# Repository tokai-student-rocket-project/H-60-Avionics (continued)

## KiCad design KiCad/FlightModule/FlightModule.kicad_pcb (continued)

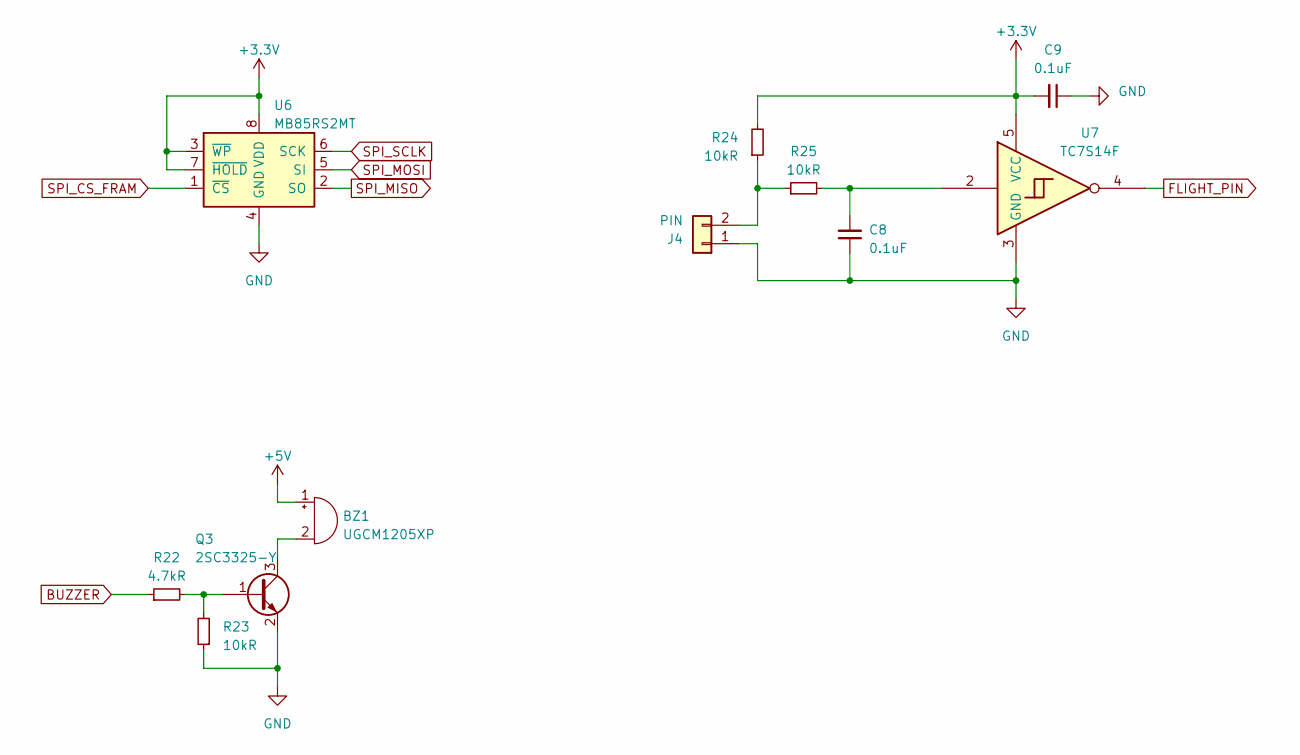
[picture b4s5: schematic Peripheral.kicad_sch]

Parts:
BZ1: UGCM1205XP; Buzzer_12x9.5RM7.6
C8, C9: 0.1uF; C_0603_1608Metric_Pad1.08x0.95mm_HandSolder
J4: PIN; Hirose_DF1B
Q3: 2SC3325-Y; SC-59_Handsoldering
R22: 4.7kR; R_0603_1608Metric_Pad0.98x0.95mm_HandSolder
R23, R24, R25: 10kR; R_0603_1608Metric_Pad0.98x0.95mm_HandSolder
U6: MB85RS2MT; DIP-8_W7.62mm
U7: TC7S14F; TSOT-23-5_HandSoldering

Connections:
+3.3V: C9.2, R24.2, U6.3 (~WP), U6.7 (~HOLD), U6.8 (VDD), U7.5 (VCC); also elsewhere on the board
+5V: BZ1.1 (-); also elsewhere on the board
BUZZER: R22.1; also elsewhere on the board
FLIGHT_PIN: U7.4; also elsewhere on the board
GND: C8.1, C9.1, J4.1, Q3.2 (E), R23.1, U6.4 (GND), U7.3 (GND); also elsewhere on the board
unnamed: BZ1.2 (+), Q3.3 (C)
unnamed: C8.2, R25.2, U7.2
unnamed: J4.2, R24.1, R25.1
unnamed: Q3.1 (B), R22.2, R23.2
SPI_CS_FRAM: U6.1 (~CS); also elsewhere on the board
SPI_MISO: U6.2 (SO); also elsewhere on the board
SPI_MOSI: U6.5 (SI); also elsewhere on the board
SPI_SCLK: U6.6 (SCK); also elsewhere on the board

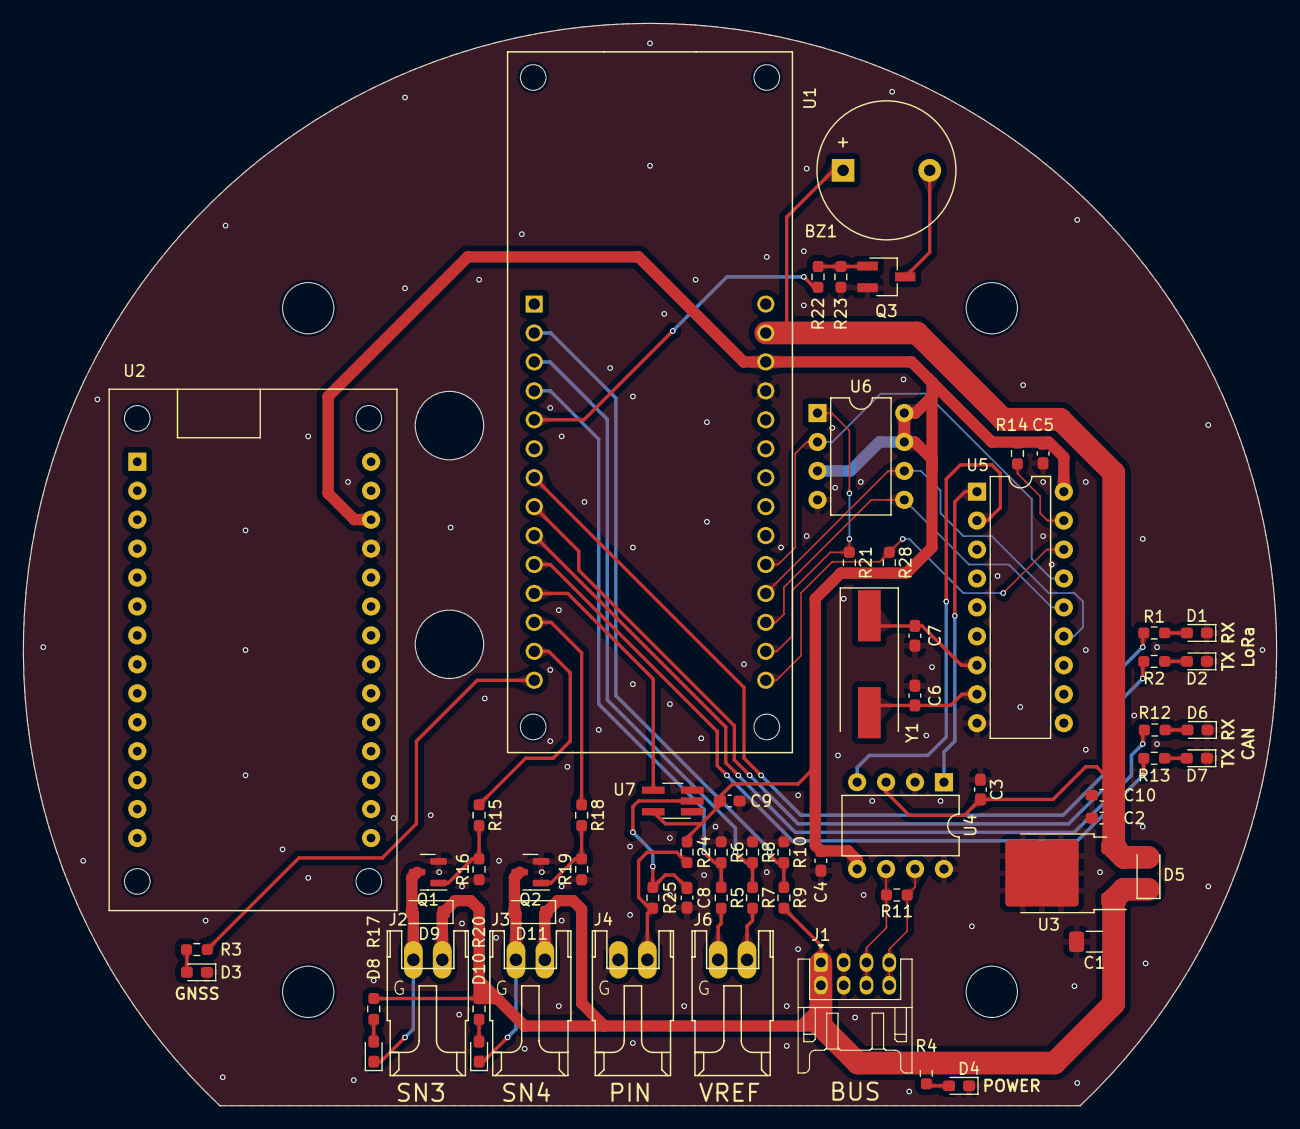
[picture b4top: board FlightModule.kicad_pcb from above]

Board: 2 copper layers, 110.0 x 95.0 mm, 64 parts (0 on the bottom side), 46 nets.

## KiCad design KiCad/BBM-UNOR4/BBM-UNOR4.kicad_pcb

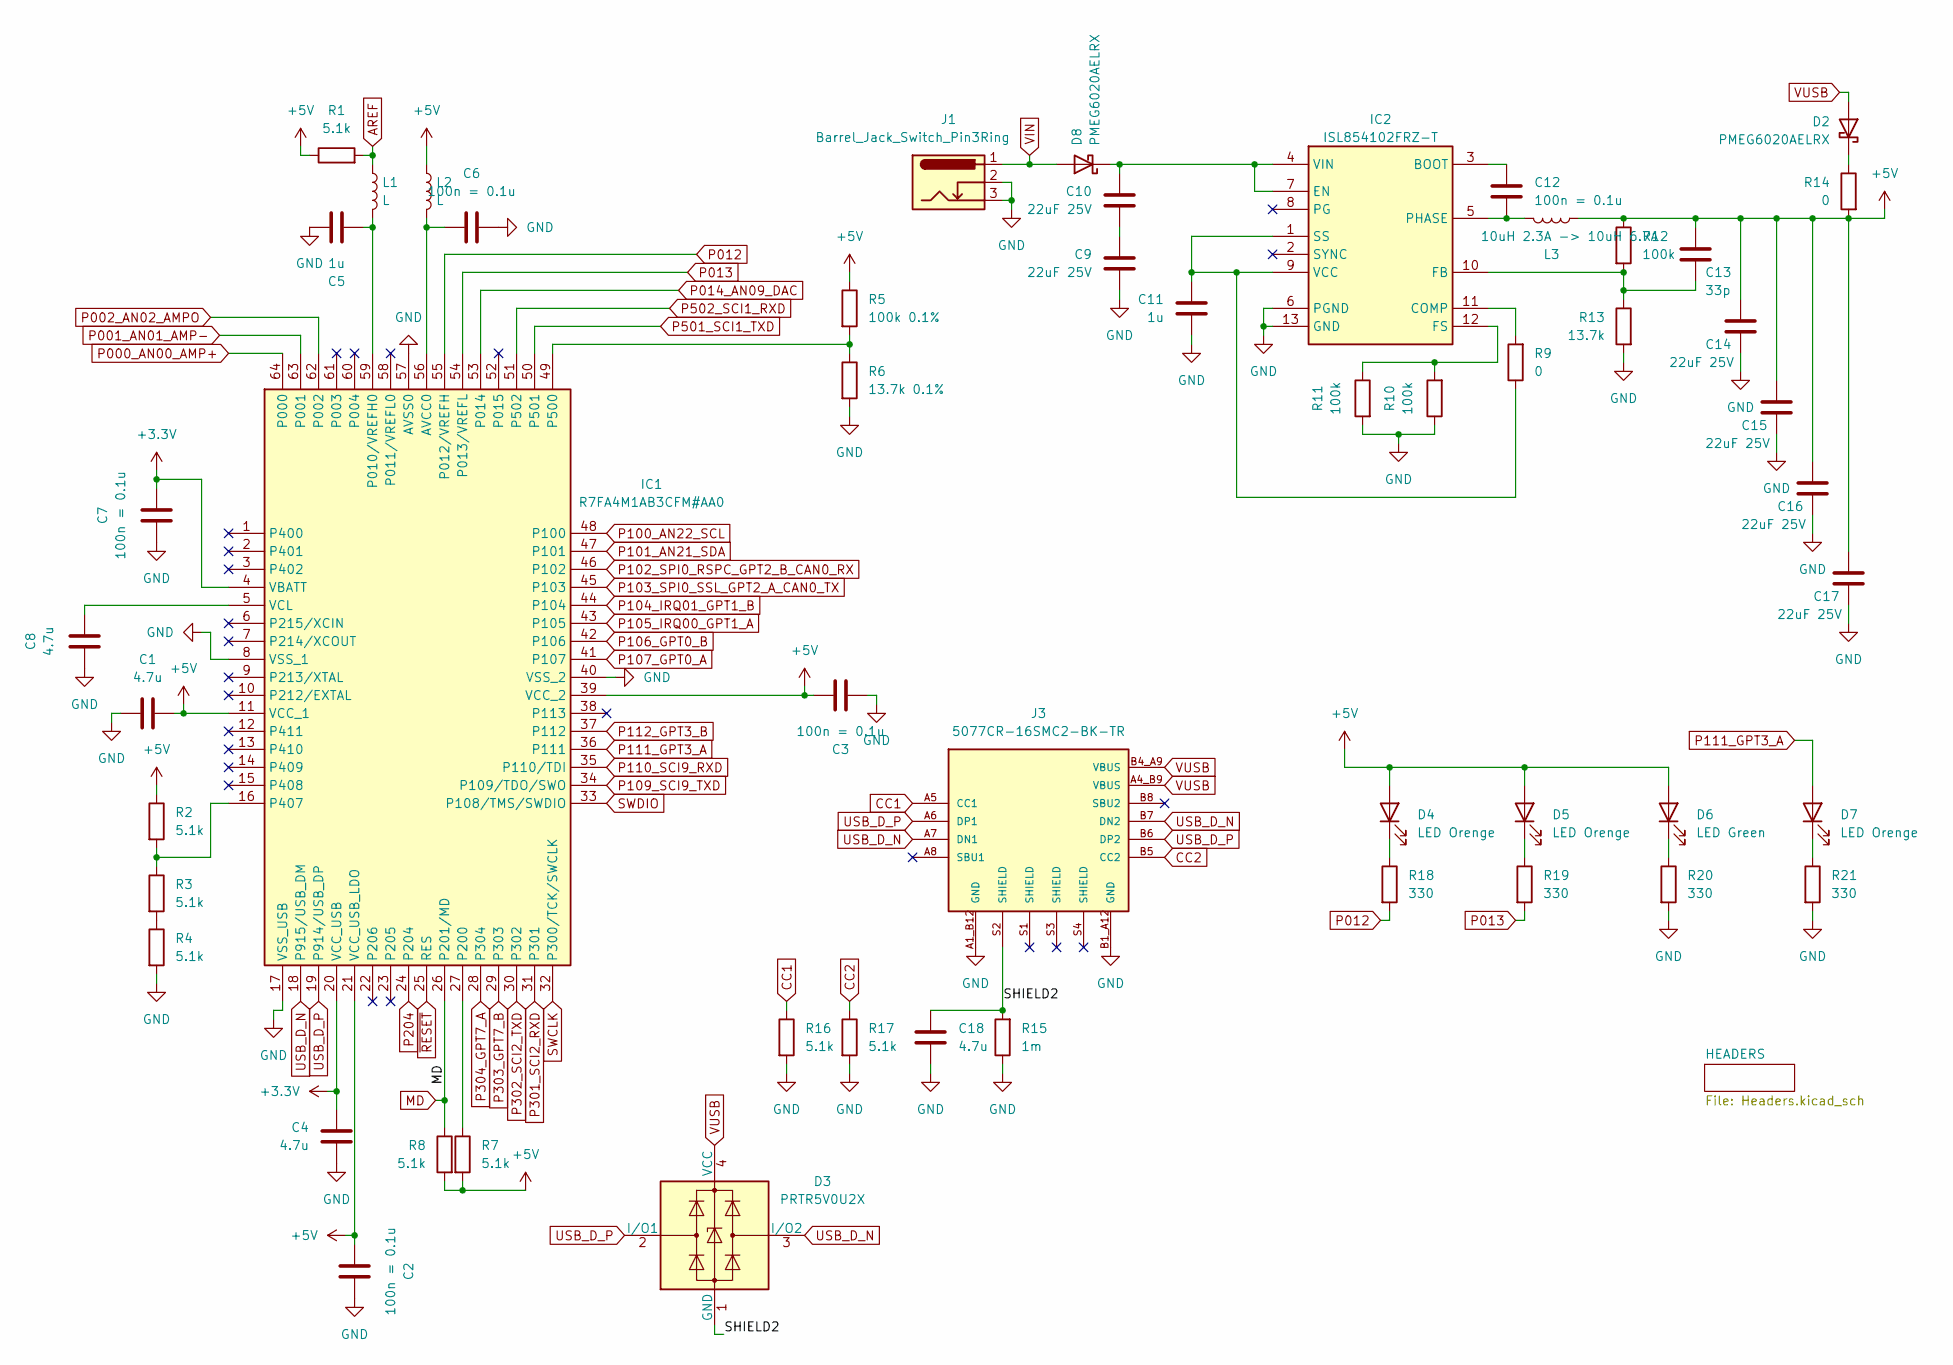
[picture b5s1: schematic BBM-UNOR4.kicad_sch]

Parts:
C1, C4, C8, C18: 4.7u; C_0805_2012Metric
C2, C3, C6, C7, C12: 100n = 0.1u; C_0603_1608Metric
C5, C11: 1u; C_0603_1608Metric
C9, C10, C14, C15, C16, C17: 22uF 25V; C_0805_2012Metric
C13: 33p; C_0603_1608Metric
D2, D8: PMEG6020AELRX; Nexperia_CFP3_SOD-123W
D3: PRTR5V0U2X; SOT-143
D4, D5, D7: LED Orenge; LED_0603_1608Metric
D6: LED Green; LED_0603_1608Metric
IC1: R7FA4M1AB3CFM#AA0; QFP50P1200X1200X170-64N; Manufacturer_Part_Number R7FA4M1AB3CFM#AA0; Mouser Part Number 968-7FA4M1AB3CFM#AA0
IC2: ISL854102FRZ-T; SON50P300X400X100-13N-D; Manufacturer_Part_Number ISL854102FRZ-T; Mouser Part Number 968-ISL854102FRZ-T
J1: Barrel_Jack_Switch_Pin3Ring; BarrelJack_Horizontal
J3: 5077CR-16SMC2-BK-TR; NELTRON_5077CR-16SMC2-BK-TR
L1, L2: L; C_0603_1608Metric
L3: 10uH 2.3A -> 10uH 6.7A; L_12x12mm_H8mm
R1, R2, R3, R4, R7, R8, R16, R17: 5.1k; R_0603_1608Metric
R5: 100k 0.1%; R_0603_1608Metric
R6: 13.7k 0.1%; R_0603_1608Metric
R9, R14: 0; R_0603_1608Metric
R10, R11, R12: 100k; R_0603_1608Metric
R13: 13.7k; R_0603_1608Metric
R15: 1m; R_0805_2012Metric
R18, R19, R20, R21: 330; R_0603_1608Metric

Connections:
+3.3V: C4.2, C7.2, IC1.4 (VBATT), IC1.20 (VCC_USB); also elsewhere on the board
+5V: C1.2, C2.2, C3.1, C13.1, C14.1, C15.2, C16.2, C17.2, D4.2 (A), D5.2 (A), D6.2 (A), IC1.11 (VCC_1), IC1.21 (VCC_USB_LDO), IC1.39 (VCC_2), L2.1, L3.2, R1.1, R2.1, R5.1, R7.2, R8.2, R12.1, R14.2; also elsewhere on the board
/SHIELD2: C18.1, D3.1 (GND), J3.S2 (SHIELD), R15.2
AREF: L1.1, R1.2; also elsewhere on the board
CC1: J3.A5 (CC1), R16.1
CC2: J3.B5 (CC2), R17.1
GND: C1.1, C2.1, C3.2, C4.1, C5.2, C6.1, C7.1, C8.1, C9.2, C11.2, C14.2, C15.1, C16.1, C17.1, C18.2, IC1.8 (VSS_1), IC1.17 (VSS_USB), IC1.40 (VSS_2), IC1.57 (AVSS0), IC2.6 (PGND), IC2.13 (GND), J1.2, J1.3, J3.A1_B12 (GND), J3.B1_A12 (GND), R4.2, R6.2, R10.1, R11.2, R13.2, R15.1, R16.2, R17.2, R20.2, R21.2; also elsewhere on the board
MD: IC1.26 (P201/MD), R8.1; also elsewhere on the board
unnamed: C9.1, C10.2
unnamed: D2.1 (K), R14.1
unnamed: D4.1 (K), R18.1
unnamed: D5.1 (K), R19.1
unnamed: D6.1 (K), R20.1
unnamed: D7.1 (K), R21.1
unnamed: C10.1, D8.1 (K), IC2.4 (VIN), IC2.7 (EN)
unnamed: C6.2, IC1.56 (AVCC0), L2.2
unnamed: C5.1, IC1.59 (P010/VREFH0), L1.2
unnamed: IC1.27 (P200), R7.1
unnamed: IC1.16 (P407), R2.2, R3.1
unnamed: IC1.49 (P500), R5.2, R6.1
unnamed: C8.2, IC1.5 (VCL)
unnamed: C12.1, IC2.3 (BOOT)
unnamed: IC2.11 (COMP), R9.2
unnamed: C13.2, IC2.10 (FB), R12.2, R13.1
unnamed: IC2.12 (FS), R10.2, R11.1
unnamed: C12.2, IC2.5 (PHASE), L3.1
unnamed: C11.1, IC2.1 (SS), IC2.9 (VCC), R9.1
unnamed: R3.2, R4.1
P000_AN00_AMP+: IC1.64 (P000); also elsewhere on the board
P001_AN01_AMP-: IC1.63 (P001); also elsewhere on the board
P002_AN02_AMPO: IC1.62 (P002); also elsewhere on the board
P012: IC1.55 (P012/VREFH), R18.2
P013: IC1.54 (P013/VREFL), R19.2
P014_AN09_DAC: IC1.53 (P014); also elsewhere on the board
P100_AN22_SCL: IC1.48 (P100); also elsewhere on the board
P101_AN21_SDA: IC1.47 (P101); also elsewhere on the board
P102_SPI0_RSPC_GPT2_B_CAN0_RX: IC1.46 (P102); also elsewhere on the board
P103_SPI0_SSL_GPT2_A_CAN0_TX: IC1.45 (P103); also elsewhere on the board
P104_IRQ01_GPT1_B: IC1.44 (P104); also elsewhere on the board
P105_IRQ00_GPT1_A: IC1.43 (P105); also elsewhere on the board
P106_GPT0_B: IC1.42 (P106); also elsewhere on the board
P107_GPT0_A: IC1.41 (P107); also elsewhere on the board
P109_SCI9_TXD: IC1.34 (P109/TDO/SWO); also elsewhere on the board
P110_SCI9_RXD: IC1.35 (P110/TDI); also elsewhere on the board
P111_GPT3_A: D7.2 (A), IC1.36 (P111); also elsewhere on the board
P112_GPT3_B: IC1.37 (P112); also elsewhere on the board
P204: IC1.24 (P204)
P301_SCI2_RXD: IC1.31 (P301); also elsewhere on the board
P302_SCI2_TXD: IC1.30 (P302); also elsewhere on the board
P303_GPT7_B: IC1.29 (P303); also elsewhere on the board
P304_GPT7_A: IC1.28 (P304); also elsewhere on the board
P501_SCI1_TXD: IC1.50 (P501)
P502_SCI1_RXD: IC1.51 (P502)
SWCLK: IC1.32 (P300/TCK/SWCLK)
SWDIO: IC1.33 (P108/TMS/SWDIO)
USB_D_N: D3.3 (I/O2), IC1.18 (P915/USB_DM), J3.A7 (DN1), J3.B7 (DN2)
USB_D_P: D3.2 (I/O1), IC1.19 (P914/USB_DP), J3.A6 (DP1), J3.B6 (DP2)
VIN: D8.2 (A), J1.1; also elsewhere on the board
VUSB: D2.2 (A), D3.4 (VCC), J3.A4_B9 (VBUS), J3.B4_A9 (VBUS)
~RESET: IC1.25 (RES); also elsewhere on the board

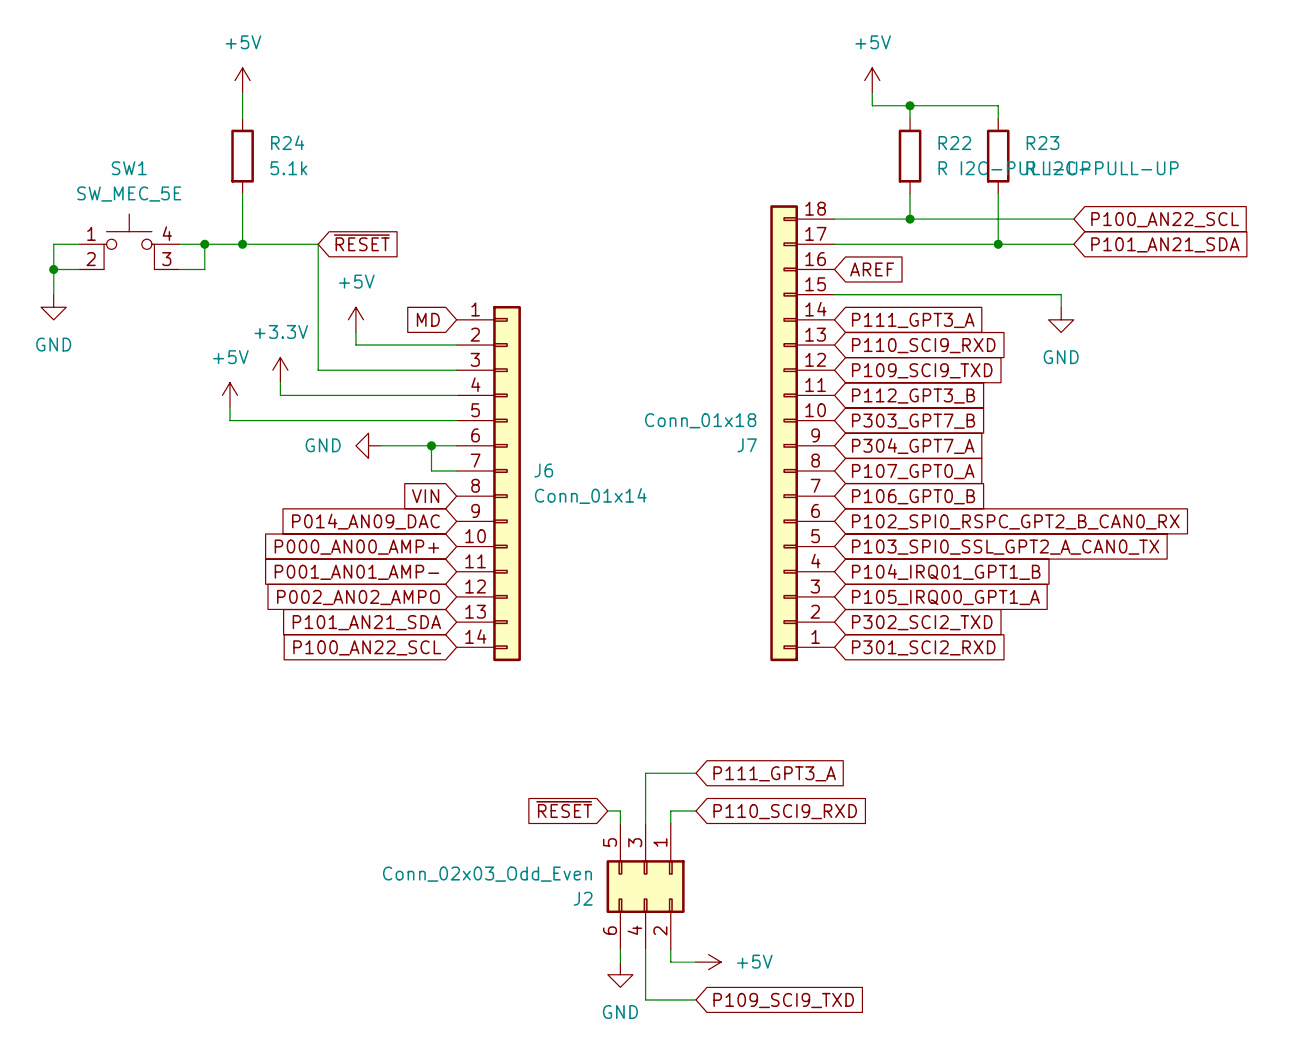
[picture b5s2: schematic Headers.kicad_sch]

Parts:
J2: Conn_02x03_Odd_Even; IDC-Header_2x03_P2.54mm_Vertical
J6: Conn_01x14; PinSocket_1x14_P2.54mm_Vertical
J7: Conn_01x18; PinSocket_1x18_P2.54mm_Vertical
R22, R23: R I2C-PULL-UP; R_0603_1608Metric
R24: 5.1k; R_0603_1608Metric
SW1: SW_MEC_5E; SMT_4.2X3.2_

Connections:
+3.3V: J6.4; also elsewhere on the board
+5V: J2.2, J6.2, J6.5, R22.1, R23.1, R24.1; also elsewhere on the board
AREF: J7.16; also elsewhere on the board
GND: J2.6, J6.6, J6.7, J7.15, SW1.1, SW1.2; also elsewhere on the board
MD: J6.1; also elsewhere on the board
P000_AN00_AMP+: J6.10; also elsewhere on the board
P001_AN01_AMP-: J6.11; also elsewhere on the board
P002_AN02_AMPO: J6.12; also elsewhere on the board
P014_AN09_DAC: J6.9; also elsewhere on the board
P100_AN22_SCL: J6.14, J7.18, R22.2; also elsewhere on the board
P101_AN21_SDA: J6.13, J7.17, R23.2; also elsewhere on the board
P102_SPI0_RSPC_GPT2_B_CAN0_RX: J7.6; also elsewhere on the board
P103_SPI0_SSL_GPT2_A_CAN0_TX: J7.5; also elsewhere on the board
P104_IRQ01_GPT1_B: J7.4; also elsewhere on the board
P105_IRQ00_GPT1_A: J7.3; also elsewhere on the board
P106_GPT0_B: J7.7; also elsewhere on the board
P107_GPT0_A: J7.8; also elsewhere on the board
P109_SCI9_TXD: J2.4, J7.12; also elsewhere on the board
P110_SCI9_RXD: J2.1, J7.13; also elsewhere on the board
P111_GPT3_A: J2.3, J7.14; also elsewhere on the board
P112_GPT3_B: J7.11; also elsewhere on the board
P301_SCI2_RXD: J7.1; also elsewhere on the board
P302_SCI2_TXD: J7.2; also elsewhere on the board
P303_GPT7_B: J7.10; also elsewhere on the board
P304_GPT7_A: J7.9; also elsewhere on the board
VIN: J6.8; also elsewhere on the board
~RESET: J2.5, J6.3, R24.2, SW1.3 (K), SW1.4 (A); also elsewhere on the board

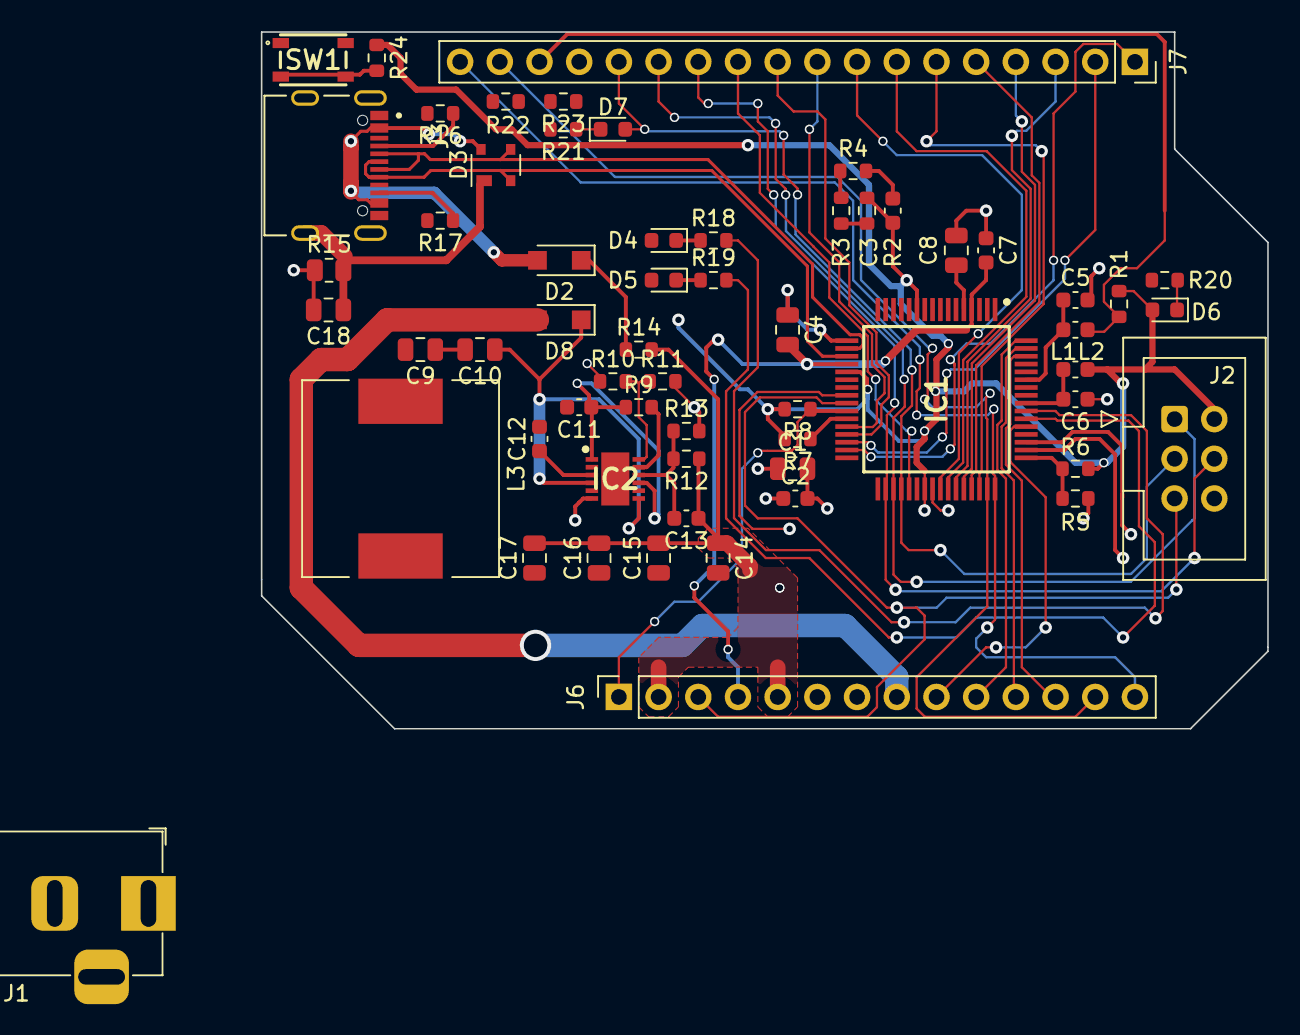
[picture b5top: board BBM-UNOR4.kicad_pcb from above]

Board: 2 copper layers, 64.4 x 44.6 mm, 60 parts (0 on the bottom side), 55 nets.

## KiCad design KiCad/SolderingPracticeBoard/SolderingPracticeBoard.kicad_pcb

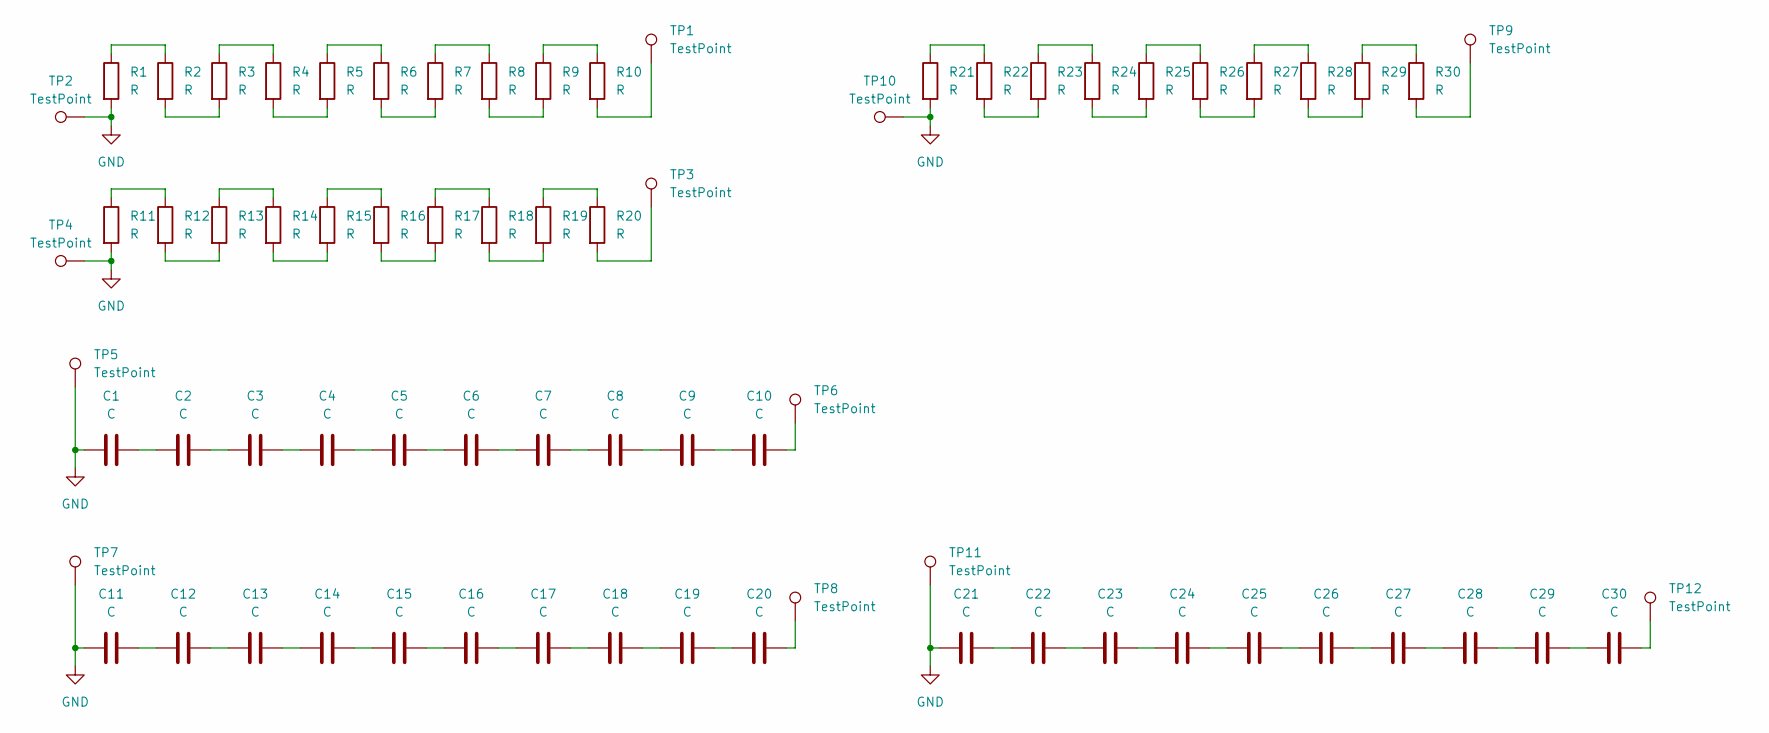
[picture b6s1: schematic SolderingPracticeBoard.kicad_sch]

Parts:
C1, C2, C3, C4, C5, C6, C7, C8, C9, C10, C11, C12, C13, C14, C15, C16, C17, C18, C19, C20, C21, C22, C23, C24, C25, C26, C27, C28, C29, C30: C; C_0603_1608Metric_Pad1.08x0.95mm_HandSolder
R1, R2, R3, R4, R5, R6, R7, R8, R9, R10, R11, R12, R13, R14, R15, R16, R17, R18, R19, R20, R21, R22, R23, R24, R25, R26, R27, R28, R29, R30: R; R_0603_1608Metric_Pad0.98x0.95mm_HandSolder
TP1, TP2, TP3, TP4, TP5, TP6, TP7, TP8, TP9, TP10, TP11, TP12: TestPoint; TestPoint_Pad_D2.0mm

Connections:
GND: C1.1, C11.1, C21.1, R1.2, R11.2, R21.2, TP2.1, TP4.1, TP5.1, TP7.1, TP10.1, TP11.1
unnamed: C1.2, C2.1
unnamed: C2.2, C3.1
unnamed: C3.2, C4.1
unnamed: C4.2, C5.1
unnamed: C5.2, C6.1
unnamed: C6.2, C7.1
unnamed: C7.2, C8.1
unnamed: C8.2, C9.1
unnamed: C9.2, C10.1
unnamed: C10.2, TP6.1
unnamed: C11.2, C12.1
unnamed: C12.2, C13.1
unnamed: C13.2, C14.1
unnamed: C14.2, C15.1
unnamed: C15.2, C16.1
unnamed: C16.2, C17.1
unnamed: C17.2, C18.1
unnamed: C18.2, C19.1
unnamed: C19.2, C20.1
unnamed: C20.2, TP8.1
unnamed: C21.2, C22.1
unnamed: C22.2, C23.1
unnamed: C23.2, C24.1
unnamed: C24.2, C25.1
unnamed: C25.2, C26.1
unnamed: C26.2, C27.1
unnamed: C27.2, C28.1
unnamed: C28.2, C29.1
unnamed: C29.2, C30.1
unnamed: C30.2, TP12.1
unnamed: R1.1, R2.1
unnamed: R2.2, R3.2
unnamed: R3.1, R4.1
unnamed: R4.2, R5.2
unnamed: R5.1, R6.1
unnamed: R6.2, R7.2
unnamed: R7.1, R8.1
unnamed: R8.2, R9.2
unnamed: R9.1, R10.1
unnamed: R10.2, TP1.1
unnamed: R11.1, R12.1
unnamed: R12.2, R13.2
unnamed: R13.1, R14.1
unnamed: R14.2, R15.2
unnamed: R15.1, R16.1
unnamed: R16.2, R17.2
unnamed: R17.1, R18.1
unnamed: R18.2, R19.2
unnamed: R19.1, R20.1
unnamed: R20.2, TP3.1
unnamed: R21.1, R22.1
unnamed: R22.2, R23.2
unnamed: R23.1, R24.1
unnamed: R24.2, R25.2
unnamed: R25.1, R26.1
unnamed: R26.2, R27.2
unnamed: R27.1, R28.1
unnamed: R28.2, R29.2
unnamed: R29.1, R30.1
unnamed: R30.2, TP9.1

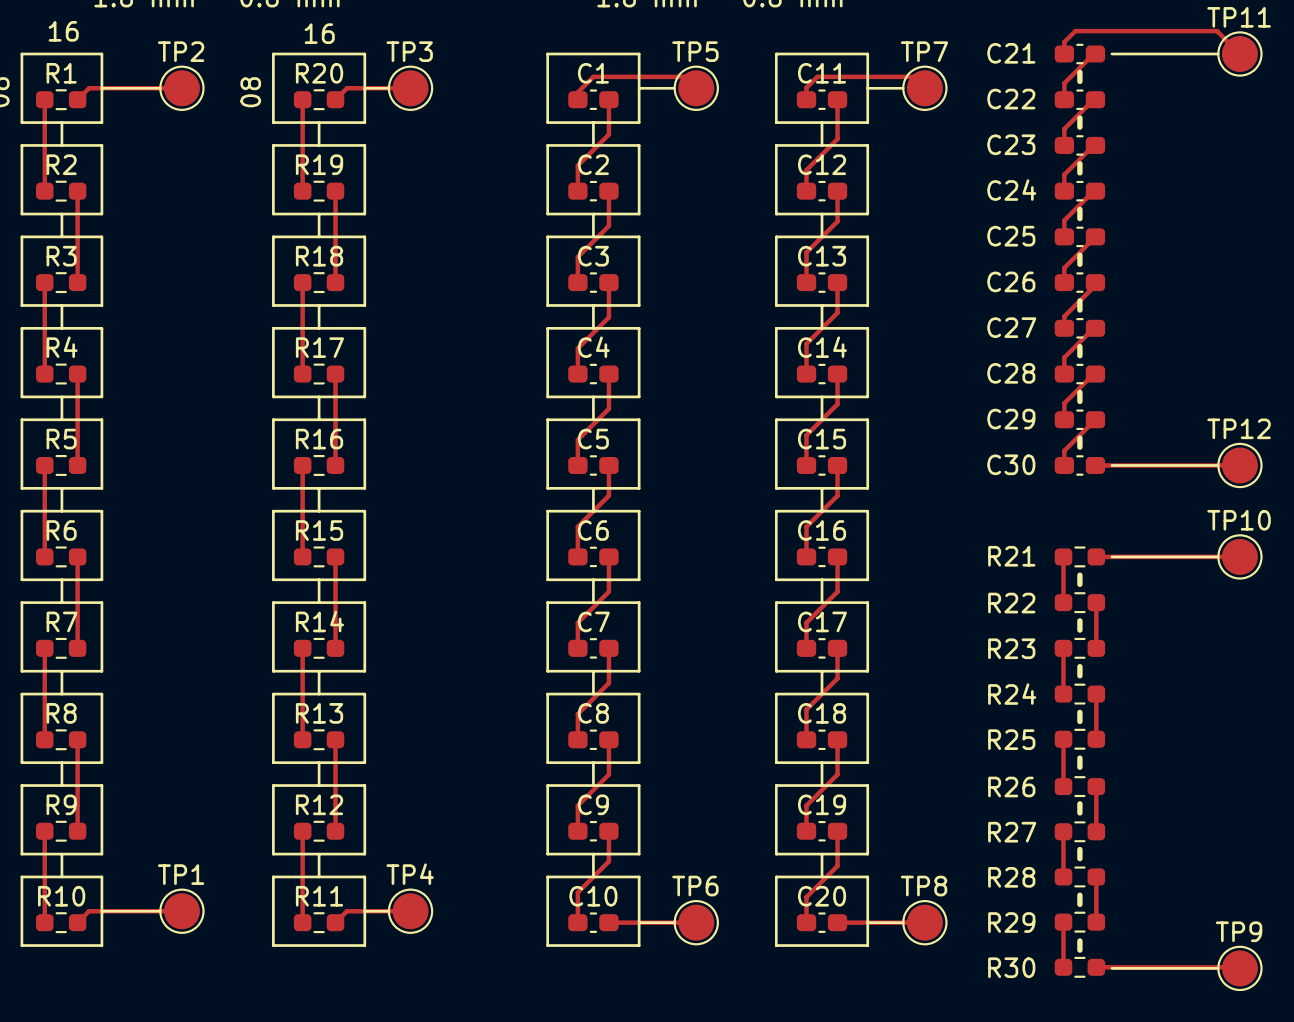
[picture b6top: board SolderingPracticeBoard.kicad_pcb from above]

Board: 2 copper layers, 72 parts (0 on the bottom side), 61 nets.

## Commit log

2024-10-31 すばる1.2開発開始
2024-10-31 Slackへの通知テスト
2024-10-31 FlightModuleのコンパイル通った
2024-10-31 FlightModule.cppに名称を変更
2024-10-31 MissionModuleのコンパイル通った
2024-10-31 SensingModuleのコンパイル通った
2024-10-31 .pioをプッシュ
2024-10-31 宣戦布告
2024-10-31 buildだけ無視
2024-10-31 .pioを無視に変更
2024-10-31 キャッシュを削除
2024-10-31 再度コミット
2024-11-01 注意事項を追加
2024-11-01 ライブラリを追加
2024-11-01 PlatformIOに適応
2024-11-01 足りないメソッドを追加
2024-11-01 FlightModuleの地上局用の環境を設定
2024-11-01 必要なライブラリを追記
2024-11-01 inoからcppに変更
2024-11-01 地上局のモジュールたちの注意を追加
2024-11-01 地上局のモジュールたちの項目を追加
2024-11-02 LogDumper系のライブラリインストール方法は特殊なので注意
2024-11-02 同じディレクトリ内から削除
2024-11-02 同じディレクトリから削除
2024-11-02 LogDumperMIssionModuleの設定と注意を追加
2024-11-02 LogDumperSensingModuleの設定を追加
2024-11-05 シリアルモニターのボーレートを追記
2024-11-05 FlightMode，ValveModeを追加
2024-11-07 4世代GSEでの燃焼実験用に戻した
2024-11-07 ValveModeの受信を追加
2024-11-15 GSEからの信号に関してenum classを定義
2024-11-15 イグニッションの状態を送信する機能を追加
2024-11-15 イグニッションの状態を受けとりCANに送信する機能を追加
2024-11-15 イグニッションでFlightModeをON
2024-11-15 関数にするか代入するか悩み中
2024-11-15 ライブラリの関係から.pio/libdepsをトラッキングに含める
2024-11-15 ライブラリのエラー治るといいな．
2024-11-16 ディレクトリ構成を追加
2024-11-20 名前を変更
2024-11-25 GNSSのテスト用コードを追加
2024-11-30 GroundJSONを.cppに変更
2024-11-30 .iniにGroundのJson版を追加
2024-12-03 FlightModuleのファイル指定を変更
2024-12-03 ライブラリ追加による生成ファイルを追加
2024-12-03 多分pio/buildはプッシュすべきでないが念のため...
2024-12-04 コメントを追加
2024-12-04 インデント変更
2024-12-04 PlatformIOに対応
2024-12-04 地上局JSONバージョンを追加
2024-12-12 分離制御系のロジックを追加
2024-12-22 機能の修正
2024-12-22 論理回路図？を再度作成
2024-12-22 名前を訂正
2024-12-24 サイズを修正
2024-12-24 角度，時間，温度，電圧，負荷情報を取得できるように修正
2024-12-24 B3Mと同様の記述に変更
2024-12-26 voltageはおｋ．temperatureとpositionがなんかずれてる
2024-12-26 Positionも直した．temperatureだけやっぱりおかしい．
2024-12-26 温度変化させて傾向見ないとわからない
2025-02-08 バルブコントロールモジュールのブロック線図を更新（審査書合格）
2025-02-08 サーボモーターを脱力させるメンバ関数を追加
2025-02-08 元に戻した
2025-02-08 前回の実験で指摘されていたバグを修正
2025-02-08 気圧と高度をTeleplotで出力できる
2025-02-08 アンビリカルケーブル離脱時にWaitingモードへと遷移する事象を解決
2025-02-11 Fマクロを使用
2025-02-11 Sutegomaからの情報を削除
2025-02-12 1/4倍されていたので等倍に直した
2025-02-15 ValveDataPart3の引数を削減
2025-02-15 LoRaで受信する項目を削減
2025-02-21 LoRa, FeRAMに送信，保存するデータを間引いた
2025-02-21 温度情報を削除
2025-02-21 受け取る情報を間引いた
2025-02-21 見やすくした（はず）
2025-02-21 コメントアウトを解除
2025-03-06 フライト1に向けバルブの角度を変更
2025-03-07 3月7日フライト1の設定
2025-03-07 3月8日フライト2の設定
2025-03-20 ログ保存する項目の誤りを修正
2025-03-26 ランチクリア時のgifを追加
2025-03-26 打上げ前のコネクタの画像
2025-03-26 打上げ後のコネクタの画像
2025-03-26 グラフを多数追加
2025-03-27 報告書を追加
2025-03-27 KiCADファイルを追加
2025-03-27 READMEを更新
2025-03-27 LANDEDで全てのバルブが閉じるように変更
2025-06-01 Flight Moduleのビルド2が完成
2025-07-06 カメラの取り付け位置の関係上，ラグ位置から90度反時計回りに回したので軸が変わるはず．
